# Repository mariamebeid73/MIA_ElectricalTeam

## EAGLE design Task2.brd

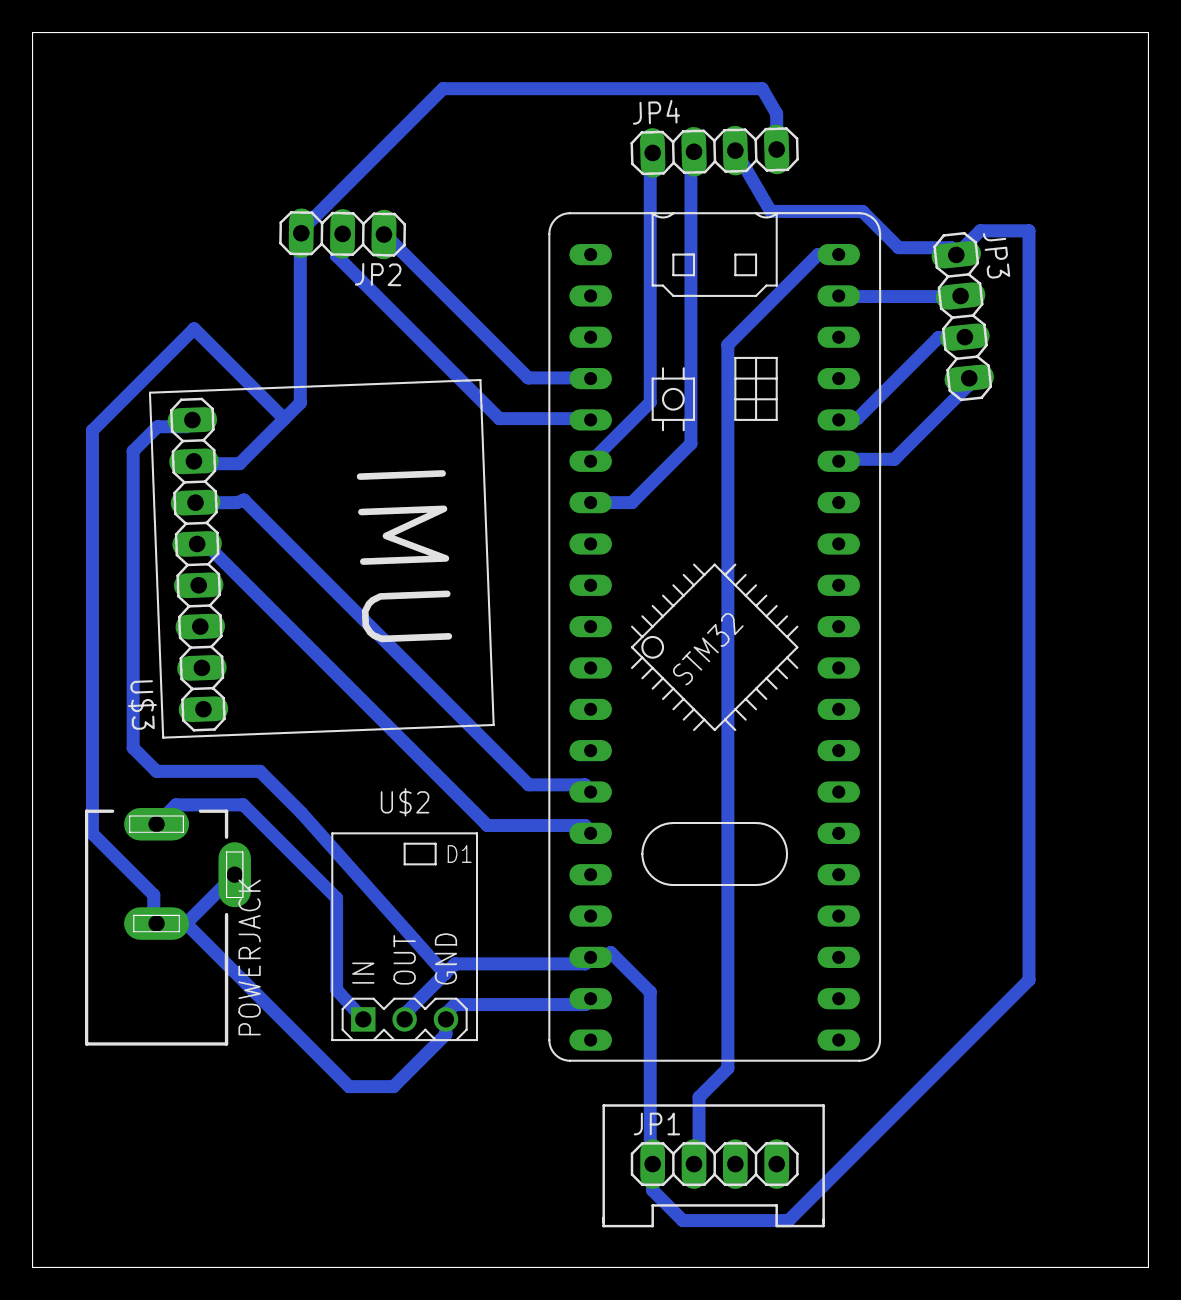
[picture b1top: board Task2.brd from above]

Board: 2 copper layers, 68.6 x 75.9 mm, 8 parts (0 on the bottom side), 13 nets.

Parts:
JP1: 1X04_DATA
JP2: 1X03
JP3, JP4: 1X04
POWERJACK: DCJ0303
U$1: BLUE_PILL
U$2: REG-AMS1117-3P-5.0V; REG-AMS1117-3P
U$3: IMU_ROBOCON_GY521; IMU_GY521

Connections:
5V: JP1.1, JP3.1, JP4.3, U$1.P$18, U$2.2, U$3.VCC
GND: JP3.2, U$1.P$22
GND1: JP1.2, U$1.P$21
GND2: JP2.3, JP4.4, POWERJACK.2, POWERJACK.3, U$1.P$19, U$2.3, U$3.GND
IN: POWERJACK.1, U$2.1
PA8: JP2.2, U$1.P$5
PA9: JP4.1, U$1.P$6
PA10: JP4.2, U$1.P$7
PB6: U$1.P$14, U$3.SCL
PB7: U$1.P$15, U$3.SDA
PB10: JP3.4, U$1.P$26
PB11: JP3.3, U$1.P$25
PB15: JP2.1, U$1.P$4

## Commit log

2022-10-22 Create Launch
